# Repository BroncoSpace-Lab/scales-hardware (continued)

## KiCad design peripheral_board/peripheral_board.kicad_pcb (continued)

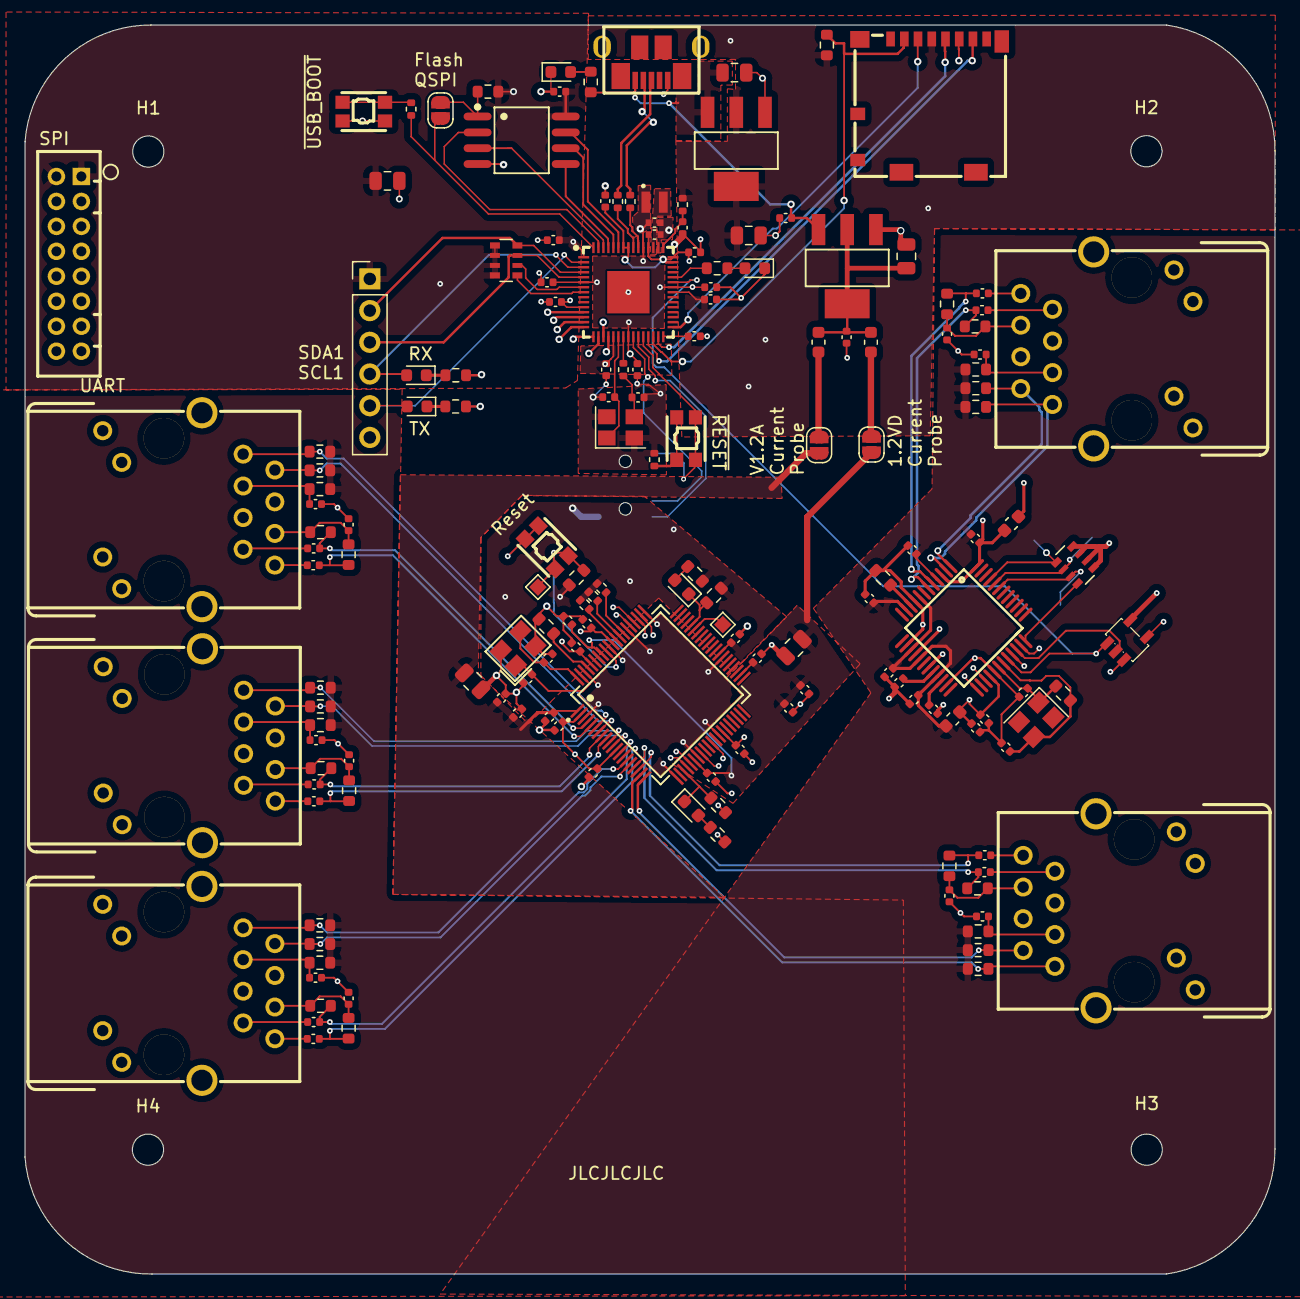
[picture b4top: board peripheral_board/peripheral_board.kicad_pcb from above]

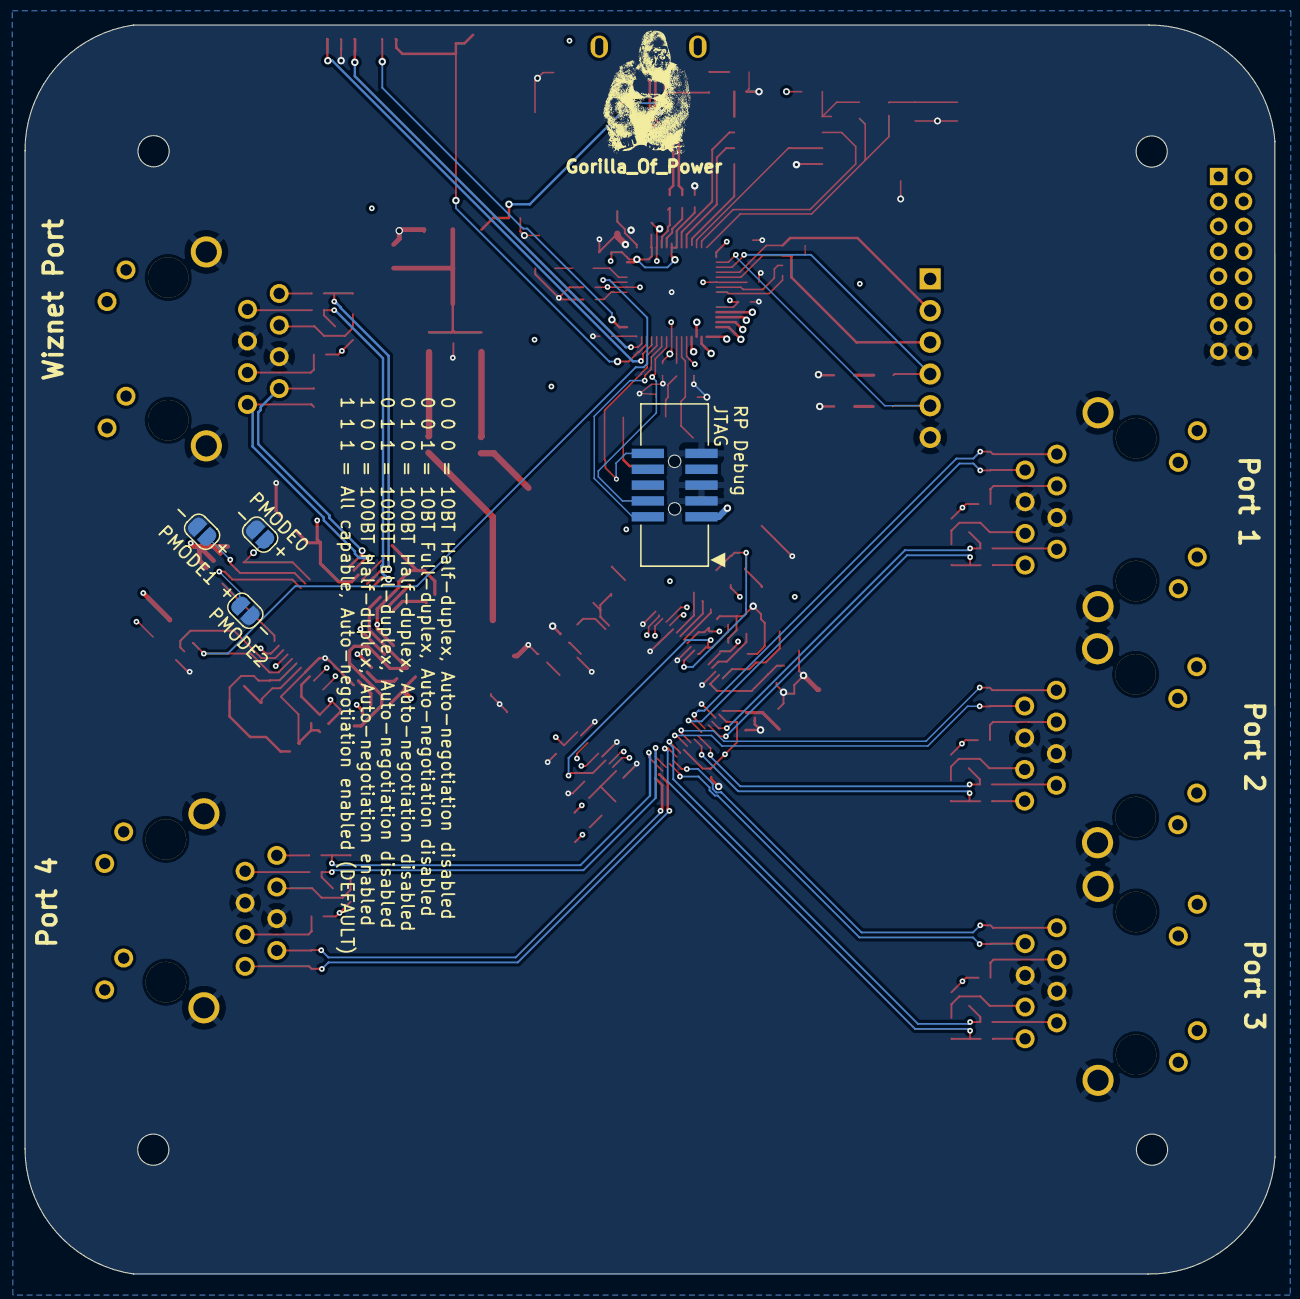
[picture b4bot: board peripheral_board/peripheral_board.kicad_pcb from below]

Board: 4 copper layers, 100.2 x 100.1 mm, 168 parts (5 on the bottom side), 128 nets.

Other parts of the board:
Gorilla_Of_Power: LOGO

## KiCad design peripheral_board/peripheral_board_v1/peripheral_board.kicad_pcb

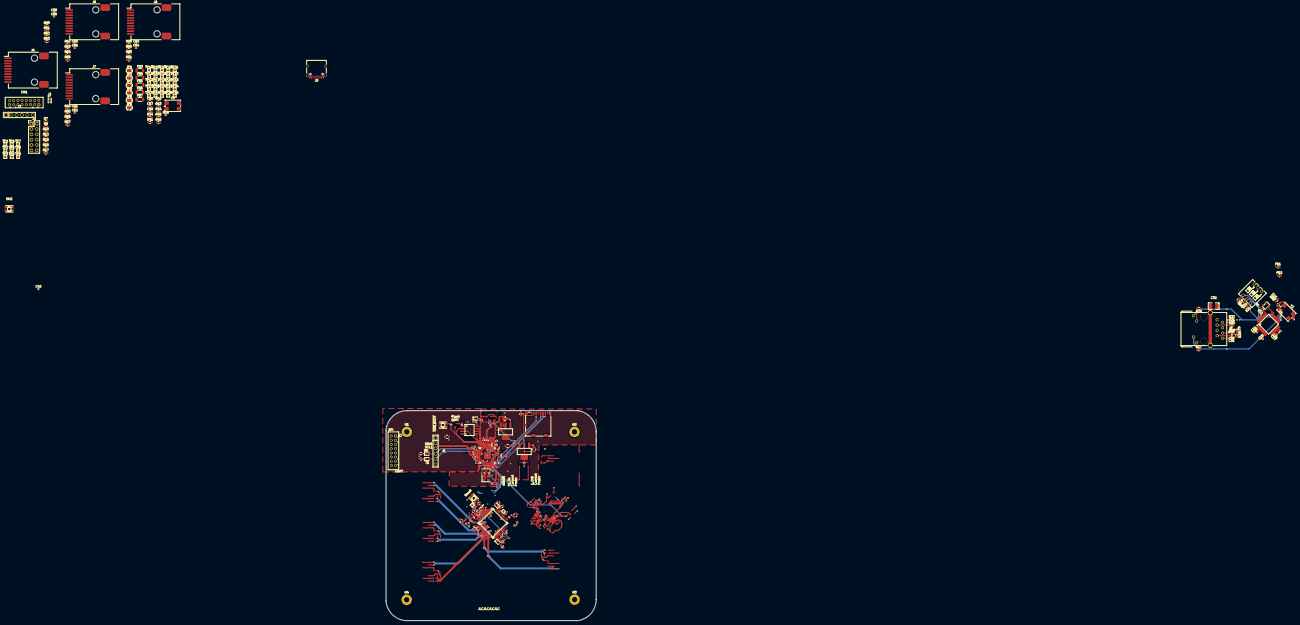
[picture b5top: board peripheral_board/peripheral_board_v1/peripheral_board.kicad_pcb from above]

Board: 4 copper layers, 100.2 x 100.1 mm, 218 parts (1 on the bottom side), 185 nets.

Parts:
C1, C2: 4.7uF; C_0402_1005Metric_small_pads
C3, C8, C9, C10, C11, C12, C13, C14, C15, C19, C34, C35, C36, C37, C38, C40, C41, C42, C45, C46, C49, C50, C51, C54, C55: 100nF; C_0402_1005Metric
C4, C5: 15pF; C_0402_1005Metric
C6, C7: 4.7uF; C_0402_1005Metric
C16, C18: 10uF; C_0805_2012Metric
C17: 22uF; C_0805_2012Metric
C20, C28: 10uF; C_0402_1005Metric
C21, C23, C24, C26, C27, C59, C60, C61, C62, C63, C64, C65, C66: 0.1uF; C_0402_1005Metric
C22, C25, C52, C53: 18pF; C_0402_1005Metric
C29, C33, C47, C48: 10nF; C_0402_1005Metric
C30, C31: 6.8nF; C_0402_1005Metric
C32: 1nF/2kV; C1210
C39, C43, C44: 100uF; C_0805_2012Metric
C56: 10uF; C_0603_1608Metric
C57, C58: 22uF; C_0603_1608Metric
CN1: Power Board Connector; CONN-TH_DF11-16DP-2DSA-08
CN2: DF11-16DP-2DSA(08); CONN-TH_DF11-16DP-2DSA-08
D1, D2, D3, D4, D5: LED; LED_0603_1608Metric
FB1, FB2: HH-1M1608-121JT; L_0603_1608Metric
FB3, FB4, FB5, FB6, FB7: FerriteBead; L_1206_3216Metric
Gorilla_Of_Power: LOGO
H1, H2, H3, H4: MountingHole; MountingHole_2.5mm_Pad
J1: Conn_01x03_Pin; PinHeader_1x03_P1.00mm_Vertical
J2, J4: Conn_01x06; HDR-TH_6P-P2.54-V-M-1
J3: Conn_02x06_Odd_Even; PinHeader_2x06_P2.54mm_Vertical
J5: USB_C_Receptacle_USB2.0_16P; USB_C_Receptacle_HRO_TYPE-C-31-M-12
J6, J7, J8, J9: RJ45_Pulse_JXD6-0001NL; RJ45_Pulse_JXD6-0001NL_Horizontal
JP1, JP2, JP3, JP4, JP5, JP6: SolderJumper_2_Open; SolderJumper-2_P1.3mm_Open_RoundedPad1.0x1.5mm
L1: 3.3uH; IND-SMD_L2.0-W1.6_AOTA-B201610S3R3-101-T
R1, R3, R4: 1k; R_0402_1005Metric
R2: 33; R_0402_1005Metric
R5, R6: 27; R_0402_1005Metric
R7, R8, R9, R10, R12, R14, R19, R20, R21, R49: 10k; R_0603_1608Metric
R11, R13, R50, R51, R52, R53, R54, R55, R56, R57, R58, R59, R60, R61, R62, R63, R64, R65: 1k; R_0603_1608Metric
R15, R34: 0; R_0603_1608Metric
R16, R17: 5.1k; R_0603_1608Metric
R18, R40: 12.4k; R_0603_1608Metric
R22, R23, R24, R33, R39: 4.7k; R_0603_1608Metric
R25: 1M; R_0603_1608Metric
R26, R28, R31, R32: 49.9; R_0603_1608Metric
R27, R29, R47, R48: 330; R_0603_1608Metric
R30: 10; R_0603_1608Metric
R35, R37: 10k; R_0402_1005Metric
R36: 4.7k; R_0402_1005Metric
R38: 350; R_0402_1005Metric
R41, R42, R43, R44, R45, R46: 750; R_0603_1608Metric
RJ1: RB1-125BAG1A; RJ45-TH_RB1-125BAG1A
SIM1: 1040310811; SIM-SMD_8P-1040310811
SW1, SW2, SW4: EVPAA602W; KEY-TH_4P-L3.5-W4.9-P2.80-LS4.3
SW3: 3_Pin_Dip_Switch_DSWB03LHGET_C25503178; SW-TH_DSWB03LHGET
TP1, TP2, TP3, TP4, TP5, TP6, TP7, TP8, TP9, TP10, TP11, TP12, TP13, TP14, TP15, TP16, TP17, TP18, TP19, TP20, TP21, TP22, TP23, TP24, TP25, TP26, TP27, TP28, TP29, TP30, TP31, TP32, TP33, TP34, TP35, TP36: TestPoint; TestPoint_Pad_1.0x1.0mm
U1: RP2350A_C42411118; QFN-60_L7.0-W7.0-P0.40-TL-EP3.4
U2: AZ1117CH-3.3TRG1; SOT-223-3_L6.5-W3.4-P2.30-LS7.0-BR
U3: W25Q128JVSIQTR; SOIC-8_L5.3-W5.3-P1.27-LS8.0-BL
U4: W5500; LQFP-48_L7.0-W7.0-P0.50-LS9.0-BL
U5: SN74AHC1G125DBVR; SOT-23-5_L3.0-W1.7-P0.95-LS2.8-BR
U6: AZ1117CH-1.2TRG1; SOT-223-3_L6.5-W3.4-P2.30-LS7.0-BR
U7: KSZ8795CLXIC; LQFP-80_L10.0-W10.0-P0.40-LS12.2-BL
Y1: ABM8-272-T3; Crystal_SMD_3225-4Pin_3.2x2.5mm
Y2: 25MHz; Crystal_SMD_7050-4Pin_7.0x5.0mm
Y3: ABMM-25.000MHZ-B2-T; Crystal_SMD_7050-4Pin_7.0x5.0mm

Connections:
1.2A: C41.2, C43.2, C45.2, C47.2, FB3.2, U7.1 (VDD12A)
1.2D: C35.2, C44.2, C46.2, C48.2, C50.2, C51.2, FB4.2, U7.26 (VDD12D), U7.42 (VDD12D), U7.73 (VDD12D)
3V3A: C23.2, C24.2, C26.2, C27.2, C28.2, FB1.2, R30.2, R31.2, R32.2, U4.4 (AVDD), U4.8 (AVDD), U4.11 (AVDD), U4.15 (AVDD), U4.17 (AVDD), U4.21 (AVDD)
+1V1: C2.1, C3.1, C6.1, C8.1, L1.1, U1.6 (DVDD), U1.23 (DVDD), U1.39 (DVDD), U1.50 (VREG_FB)
+3V3: C1.1, C9.1, C10.1, C11.1, C12.1, C13.1, C14.1, C15.1, C17.2, C18.1, C19.1, CN2.1, CN2.2, FB1.1, FB6.1, FB7.1, J2.1, J3.1, J3.2, J4.1, R2.2, R7.2, R9.2, R10.2, R12.2, R14.2, R15.2, R19.2, R20.2, R21.2, R22.2, R23.2, R24.2, R27.2, R29.1, R47.2, R48.2, R50.2, R52.2, R54.2, R56.2, R58.2, R60.2, R62.2, R64.2, SIM1.4 (VDD), U1.1 (IOVDD), U1.11 (IOVDD), U1.20 (IOVDD), U1.30 (IOVDD), U1.38 (IOVDD), U1.44 (ADC_AVDD), U1.45 (IOVDD), U1.49 (VREG_VIN), U1.53 (USB_OTP_VDD), U1.54 (QSPI_IOVDD), U2.2 (Vout), U2.4 (Vout), U3.1 (~CS), U3.8 (VCC), U4.28 (VDD), U5.5 (VCC)
/Raspberry_pi/ QSPI_SS: R1.1, R15.1, U1.60 (QSPI_SS)
/Raspberry_pi/QSPI_DATA_0: U1.57 (QSPI_SD0), U3.5 (DI)
/Raspberry_pi/QSPI_DATA_1: U1.59 (QSPI_SD1), U3.2 (DO)
/Raspberry_pi/QSPI_DATA_2: U1.58 (QSPI_SD2), U3.3 (IO2)
/Raspberry_pi/QSPI_DATA_3: U1.55 (QSPI_SD3), U3.7 (IO3)
/Raspberry_pi/QSPI_SCK: U1.56 (QSPI_SCLK), U3.6 (CLK)
/Raspberry_pi/~USB_BOOT: R1.2, SW1.1'
CGND: C32.1, RJ1.13 (GND), RJ1.14 (GND)
Chassis_GND: FB5.1, J6.SH, J7.SH, J8.SH, J9.SH
D+: J5.A6 (D+), J5.B6 (D+), R5.1
D-: J5.A7 (D-), J5.B7 (D-), R6.1
GND: C1.2, C2.2, C3.2, C4.1, C5.1, C6.2, C7.2, C8.2, C9.2, C10.2, C11.2, C12.2, C13.2, C14.2, C15.2, C16.1, C17.1, C18.2, C19.2, C22.1, C25.1, C32.2, C34.1, C35.1, C36.1, C37.1, C38.1, C39.1, C40.1, C41.1, C42.1, C43.1, C44.1, C45.1, C46.1, C47.1, C48.1, C49.1, C50.1, C51.1, C52.2, C53.2, C54.1, C55.1, C56.2, C57.2, C58.2, C59.2, C60.2, C61.2, C62.2, C63.2, C64.2, C65.2, C66.2, CN1.9, CN1.11, CN1.13, CN1.15, CN2.15, CN2.16, D1.1 (K), FB2.1, FB5.2, J1.2, J2.6, J4.6, J5.A1 (GND), J5.A12 (GND), J5.B1 (GND), J5.B12 (GND), J5.S1 (SHIELD), R11.2, R13.2, R16.1, R17.1, R38.2, R40.2, R41.2, R42.2, R43.2, R44.2, R45.2, R46.2, R51.2, R53.2, R55.2, R57.2, R59.2, R61.2, R63.2, R65.2, RJ1.4, RJ1.5, SIM1.6 (VSS), SW1.2, SW2.2, SW3.4, SW3.5, SW3.6, SW4.2, U1.47 (VREG_PGND), U1.61 (GND), U2.1 (ADJ/GND), U3.4 (GND), U4.23 (RSVD), U4.29 (GND), U5.3 (GND), U6.1 (GND), U7.3 (GNDA), U7.21 (GNDA), U7.27 (GNDD), U7.33 (GNDD), U7.47 (GNDD), U7.61 (GNDD), U7.71 (GNDD), U7.78 (GNDA), Y1.2, Y1.4, Y2.2, Y2.4, Y3.2, Y3.4
GNDA: C20.2, C21.2, C23.1, C24.1, C26.1, C27.1, C28.1, C29.1, C33.1, FB2.2, R18.1, U4.3 (AGND), U4.9 (AGND), U4.14 (AGND), U4.16 (AGND), U4.19 (AGND), U4.48 (AGND)
GPIO14: CN1.14, U1.18 (GPIO14)
GPIO15: CN1.16, U1.19 (GPIO15)
GPIO22: J3.3, U1.34 (GPIO22)
GPIO23: J3.5, U1.35 (GPIO23)
GPIO24: J3.7, U1.36 (GPIO24)
GPIO25: J3.9, U1.37 (GPIO25)
GPIO26_ADC0: J3.4, U1.40 (GPIO26_ADC0)
GPIO27_ADC1: J3.6, U1.41 (GPIO27_ADC1)
GPIO28_ADC2: J3.8, U1.42 (GPIO28_ADC2)
GPIO29_ADC3: J3.10, U1.43 (GPIO29_ADC3)
GREEN_LED: RJ1.10 (LLED-), U4.25 (LINKLED)
I2C0_SCL: J2.2, R7.1, U1.8 (GPIO5)
I2C0_SDA: J2.3, R9.1, U1.7 (GPIO4)
I2C1_SCL: J2.4, J4.3, R10.1, U1.5 (GPIO3)
I2C1_SDA: J2.5, J4.2, R12.1, U1.4 (GPIO2)
INTR_N: D4.1 (K), R33.2, U7.23 (INTR_N)
INTn: R23.1, U1.33 (GPIO21), U4.36 (INTn)
LED1_0: J6.1, J6.9, JP1.1 (A), R51.1, R53.1, U7.65 (LED10)
LED1_1: JP2.1 (A), U7.64 (LED11)
LED2_0: J7.1, J7.9, JP3.1 (A), R55.1, R57.1, U7.63 (LED20)
LED2_1: JP4.1 (A), U7.62 (LED21)
LED3_0: J8.1, J8.9, JP5.1 (A), R59.1, R61.1, U7.25 (LED3_0)
LED3_1: JP6.1 (A), U7.24 (LED3_1)
LED4_0: J9.1, J9.9, R63.1, R65.1, U7.31 (LED4_0)
unnamed: C5.2, R4.1, Y1.3
unnamed: C30.2, RJ1.7
unnamed: C31.2, RJ1.8
unnamed: C39.2, C40.2, C42.2, FB3.1, FB4.1, U6.2 (VOUT), U6.4 (VOUT)
unnamed: C52.1, R34.2, Y3.1
unnamed: CN1.4, TP5.1
unnamed: CN1.6, TP6.1
unnamed: CN1.8, TP7.1
unnamed: CN1.10, TP8.1
unnamed: CN1.12, TP9.1
unnamed: D1.2 (A), R8.1
unnamed: D2.1 (K), R11.1
unnamed: D3.1 (K), R13.1
unnamed: D4.2 (A), R47.1
unnamed: D5.2 (A), R48.1
unnamed: J3.11, J3.12
unnamed: J5.A5 (CC1), R16.2
unnamed: J5.B5 (CC2), R17.2
unnamed: J6.2, R52.1
unnamed: J6.10, R50.1
unnamed: J7.2, R56.1
unnamed: J7.10, R54.1
unnamed: J8.2, R60.1
unnamed: J8.10, R58.1
unnamed: J9.2, R64.1
unnamed: J9.10, R62.1
unnamed: JP1.2 (B), R41.1
unnamed: JP2.2 (B), R42.1
unnamed: JP3.2 (B), R43.1
unnamed: JP4.2 (B), R44.1
unnamed: JP5.2 (B), R45.1
unnamed: JP6.2 (B), R46.1
unnamed: R3.2, SW2.1'
unnamed: R29.2, RJ1.9 (LLED+)
unnamed: R27.1, RJ1.11 (RLED+)
unnamed: SW1.1, TP2.1
unnamed: SW1.2', TP3.1
unnamed: SW2.1, TP1.1
unnamed: SW2.2', TP4.1
unnamed: SW4.1', TP35.1
unnamed: SW4.2', TP36.1
unnamed: R3.1, U1.26 (RUN)
unnamed: R6.2, U1.51 (USB_DM)
unnamed: R5.2, U1.52 (USB_DP)
unnamed: C7.1, R2.1, U1.46 (VREG_AVDD)
unnamed: L1.2, U1.48 (VREG_LX)
unnamed: C4.2, U1.21 (XIN), Y1.1
unnamed: R4.2, U1.22 (XOUT)
unnamed: C21.1, U4.22 (1V2O)
unnamed: R18.2, U4.10 (EXRES1)
unnamed: C20.1, U4.20 (TOCAP)
unnamed: C22.2, R25.1, U4.30 (XI/CLKIN), Y2.1
unnamed: C25.2, R25.2, U4.31 (XO), Y2.3
unnamed: TP24.1, U7.54 (COL5)
unnamed: TP25.1, U7.53 (CRS5)
unnamed: R40.1, U7.77 (ISET)
unnamed: TP23.1, U7.55 (REFCLKO)
unnamed: TP32.1, U7.44 (RXC5/GRXC5)
unnamed: TP31.1, U7.45 (RXD5_0)
unnamed: TP30.1, U7.46 (RXD5_1)
unnamed: TP29.1, U7.49 (RXD5_2)
unnamed: TP28.1, U7.50 (RXD5_3)
unnamed: TP22.1, U7.57 (RXD5_4)
unnamed: TP21.1, U7.58 (RXD5_5)
unnamed: TP20.1, U7.59 (RXD5_6)
unnamed: TP19.1, U7.60 (RXD5_7)
unnamed: TP27.1, U7.51 (RXDV5/CRSDV5/RXD5_CTL)
unnamed: TP26.1, U7.52 (RXER5)
unnamed: R37.1, U7.67 (SCL_MDC)
unnamed: R36.1, U7.68 (SDA_MDIO)
unnamed: R38.1, U7.66 (SPIQ)
unnamed: R35.1, U7.69 (SPIS_N)
unnamed: TP33.1, U7.43 (TXC5/REFCLKI5/GTXC5)
unnamed: TP11.1, U7.30 (TXD5_0)
unnamed: TP12.1, U7.32 (TXD5_1)
unnamed: TP13.1, U7.35 (TXD5_2)
unnamed: TP14.1, U7.36 (TXD5_3)
unnamed: TP16.1, U7.38 (TXD5_4)
unnamed: TP17.1, U7.39 (TXD5_5)
unnamed: TP18.1, U7.40 (TXD5_6)
unnamed: TP34.1, U7.41 (TXD5_7)
unnamed: TP10.1, U7.29 (TXEN5/TXDS5_CTL)
unnamed: TP15.1, U7.37 (TXER5)
unnamed: C53.1, U7.79 (XI), Y3.3
unnamed: R34.1, U7.80 (XO)
PME_N: D5.1 (K), R39.2, U7.56 (PME)
PMODE0: R21.1, SW3.1, U4.45 (PMODE0)
PMODE1: R20.1, SW3.2, U4.44 (PMODE1)
PMODE2: R19.1, SW3.3, U4.43 (PMODE2)
R1CT: C60.1, J6.8 (RCT)
R2CT: C62.1, J7.8 (RCT)
R3CT: C64.1, J8.8 (RCT)
R4CT: C66.1, J9.8 (RCT)
RCT: C29.2, R26.1, R28.1, RJ1.6
RST_N: C56.1, R49.2, SW4.1, U7.72 (RST_N)
RSTn: R22.1, U1.32 (GPIO20), U4.37 (RSTn)
RX: D2.2 (A), J4.4, U1.3 (GPIO1)
RX1+: J6.6 (RD+), U7.4 (RXP1)
RX1-: J6.7 (RD-), U7.5 (RXM1)
RX2+: J7.6 (RD+), U7.8 (RXP2)
RX2-: J7.7 (RD-), U7.9 (RXM2)
RX3+: J8.6 (RD+), U7.13 (RXP3)
RX3-: J8.7 (RD-), U7.14 (RXM3)
RX4+: J9.6 (RD+), U7.17 (RXP4)
RX4-: J9.7 (RD-), U7.18 (RXM4)
RX +: C30.1, R26.2, U4.6 (RXP)
RX -: C31.1, R28.2, U4.5 (RXN)
SPI0_CS1: R24.1, U4.32 (SCSn)
SPI0_CSO: R14.1, SIM1.2 (CD/DAT3), U1.28 (GPIO17)
SPI0_ETHER: U4.34 (MISO), U5.2 (A)
SPI0_MISO: SIM1.7 (DAT0), U1.27 (GPIO16), U5.4 (Y)
SPI0_MOSI: SIM1.3 (CMD), U1.31 (GPIO19), U4.35 (MOSI)
SPI0_SCK: SIM1.5 (CLK), U1.29 (GPIO18), U4.33 (SCLK), U5.1 (~OE)
SPI1_CS1: CN2.12, U1.17 (GPIO13)
SPI1_RX: CN2.8, U1.16 (GPIO12)
SPI1_SCK: CN2.10, U1.14 (GPIO10)
SPI1_TX: CN2.14, U1.15 (GPIO11)
SWCLK: J1.1, U1.24 (SWCLK)
T1CT: C59.1, J6.3 (TCT)
T2CT: C61.1, J7.3 (TCT)
T3CT: C63.1, J8.3 (TCT)
T4CT: C65.1, J9.3 (TCT)
TCT: C33.2, R30.1, RJ1.3
TX: D3.2 (A), J4.5, U1.2 (GPIO0)
TX1+: J6.4 (TD+), U7.6 (TXP1)
TX1-: J6.5 (TD-), U7.7 (TXM1)
TX2+: J7.4 (TD+), U7.10 (TXP2)
TX2-: J7.5 (TD-), U7.11 (TXM2)
TX3+: J8.4 (TD+), U7.15 (TXP3)
TX3-: J8.5 (TD-), U7.16 (TXM3)
TX4+: J9.4 (TD+), U7.19 (TXP4)
TX4-: J9.5 (TD-), U7.20 (TXM4)
TX +: R32.1, RJ1.1, U4.2 (TXP)
TX -: R31.1, RJ1.2, U4.1 (TXN)
UART1_CTS: CN2.7, U1.9 (GPIO6)
UART1_RTS: CN2.9, U1.10 (GPIO7)
UART1_RX: CN2.5, U1.13 (GPIO9)
UART1_TX: CN2.3, U1.12 (GPIO8)
VBUS: C16.2, C34.2, J5.A4 (VBUS), J5.A9 (VBUS), J5.B4 (VBUS), J5.B9 (VBUS), R8.2, U2.3 (Vin), U6.3 (INPUT)
VCC: CN1.1, CN1.3, CN1.5, CN1.7
VDDAT: C37.2, C38.2, C49.2, C57.1, FB6.2, U7.2 (VDDAT33), U7.12 (VDDAT33), U7.76 (VDDAT33)
VDDIO: C36.2, C54.2, C55.2, C58.1, FB7.2, R33.1, R35.2, R36.2, R37.2, R39.1, R49.1, U7.34 (VDDIO), U7.48 (VDDIO), U7.70 (VDDIO)
YELLOW_LED: RJ1.12 (RLED-), U4.27 (ACTLED)

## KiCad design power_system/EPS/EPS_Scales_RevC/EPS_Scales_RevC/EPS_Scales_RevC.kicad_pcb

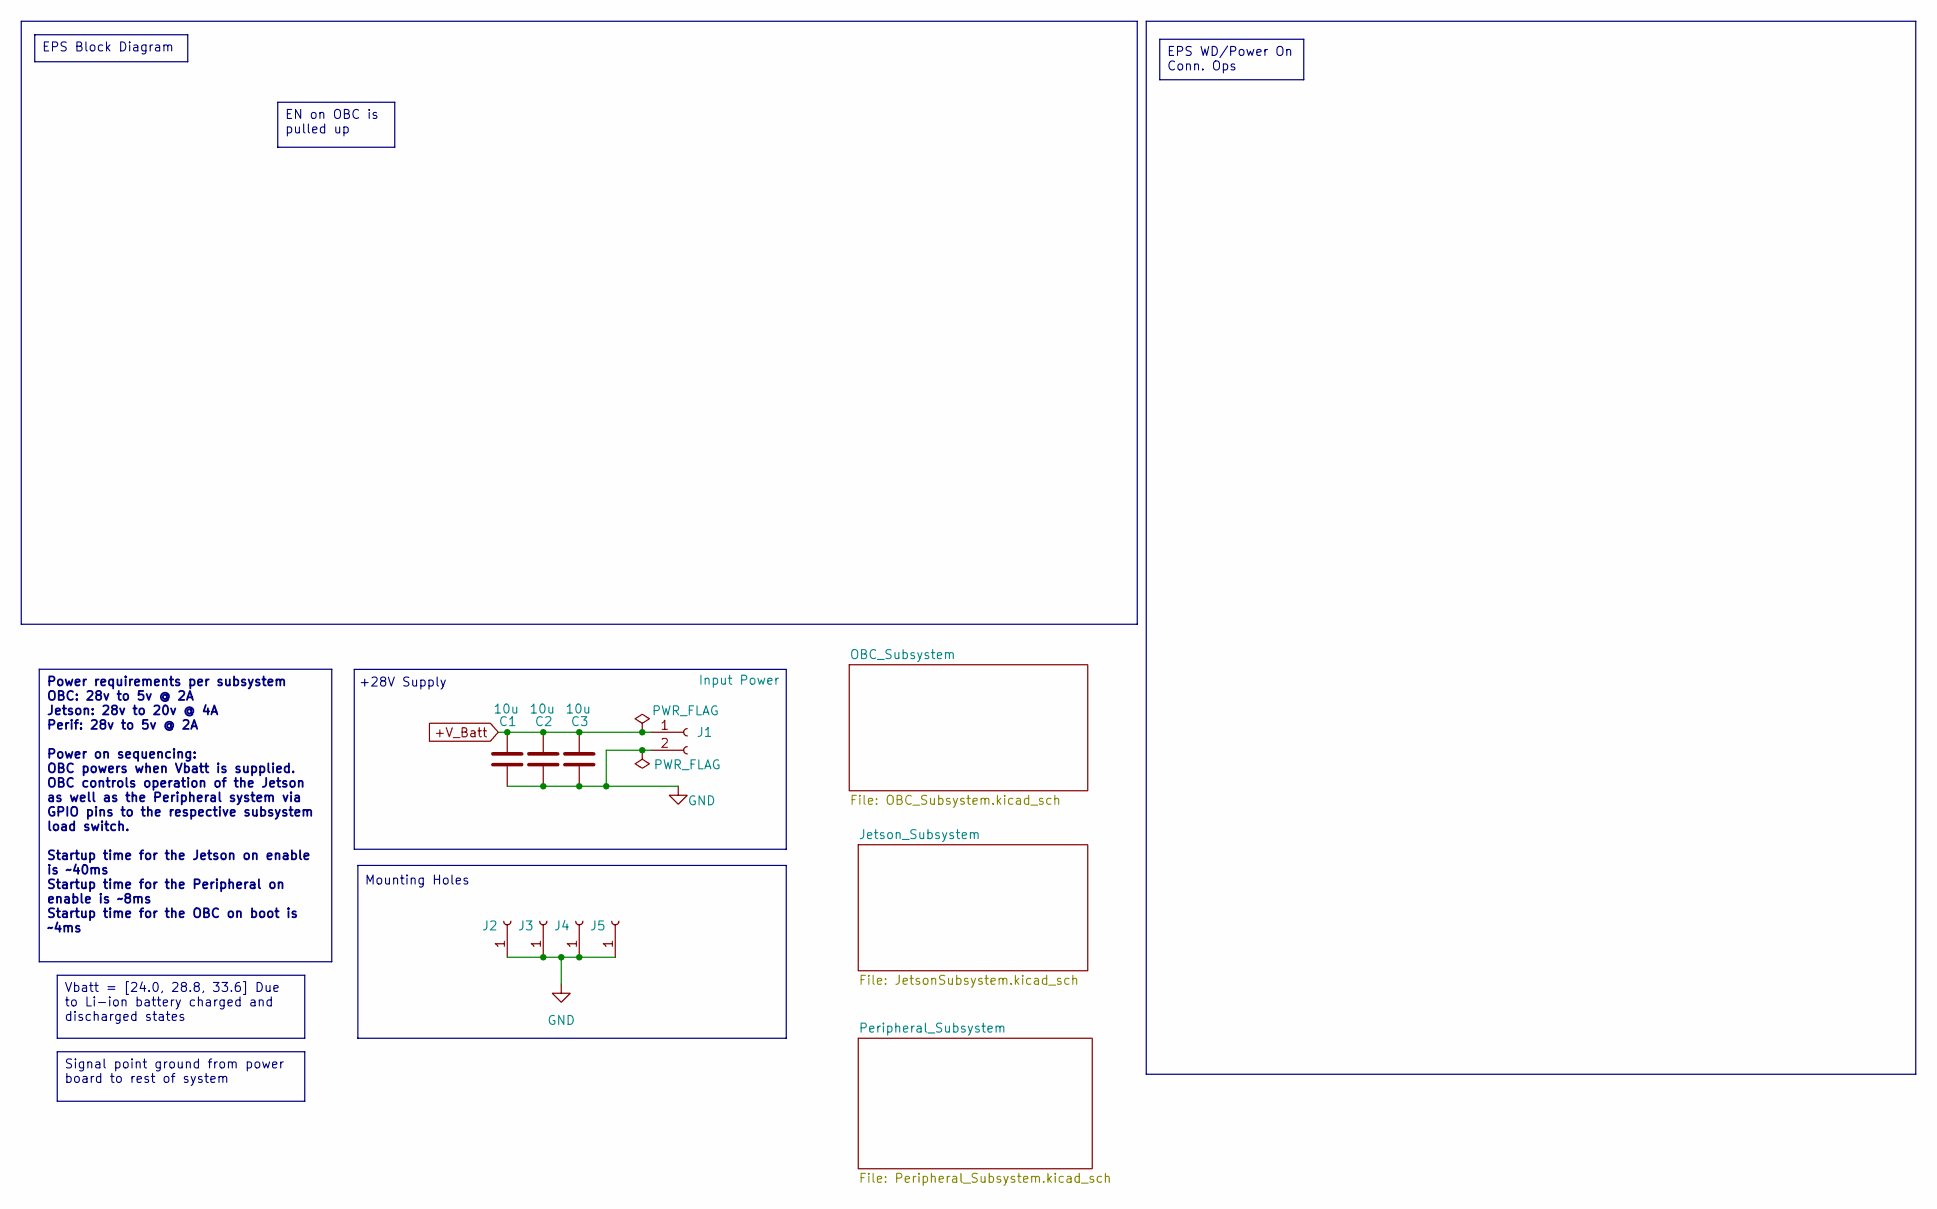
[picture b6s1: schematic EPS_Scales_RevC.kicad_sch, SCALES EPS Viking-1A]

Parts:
C1, C2, C3: 10u; C_1210_3225Metric
J1: Input Power; AMASS_XT60PW-F_1x02_P7.20mm_Horizontal
J2, J3, J4, J5: Conn_01x01_Socket; MountingHole_2.5mm_Pad_Via

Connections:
+V_Batt: C1.1, C2.1, C3.1, J1.1; also elsewhere on the board
GND: C1.2, C2.2, C3.2, J1.2, J2.1, J3.1, J4.1, J5.1; also elsewhere on the board

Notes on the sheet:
Mounting Holes
+28V Supply
Signal point ground from power board to rest of system
EPS Block Diagram
Power requirements per subsystem OBC: 28v to 5v @ 2A Jetson: 28v to 20v @ 4A Perif: 28v to 5v @ 2A Power on sequencing: OBC powers when Vbatt is supplied. OBC controls operation of the Jetson as well as the Peripheral system via GPIO pins to the respective subsystem load switch. Startup time for th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
Vbatt = [24.0, 28.8, 33.6] Due to Li-ion battery charged and discharged states
EPS WD/Power On Conn. Ops
EN on OBC is pulled up

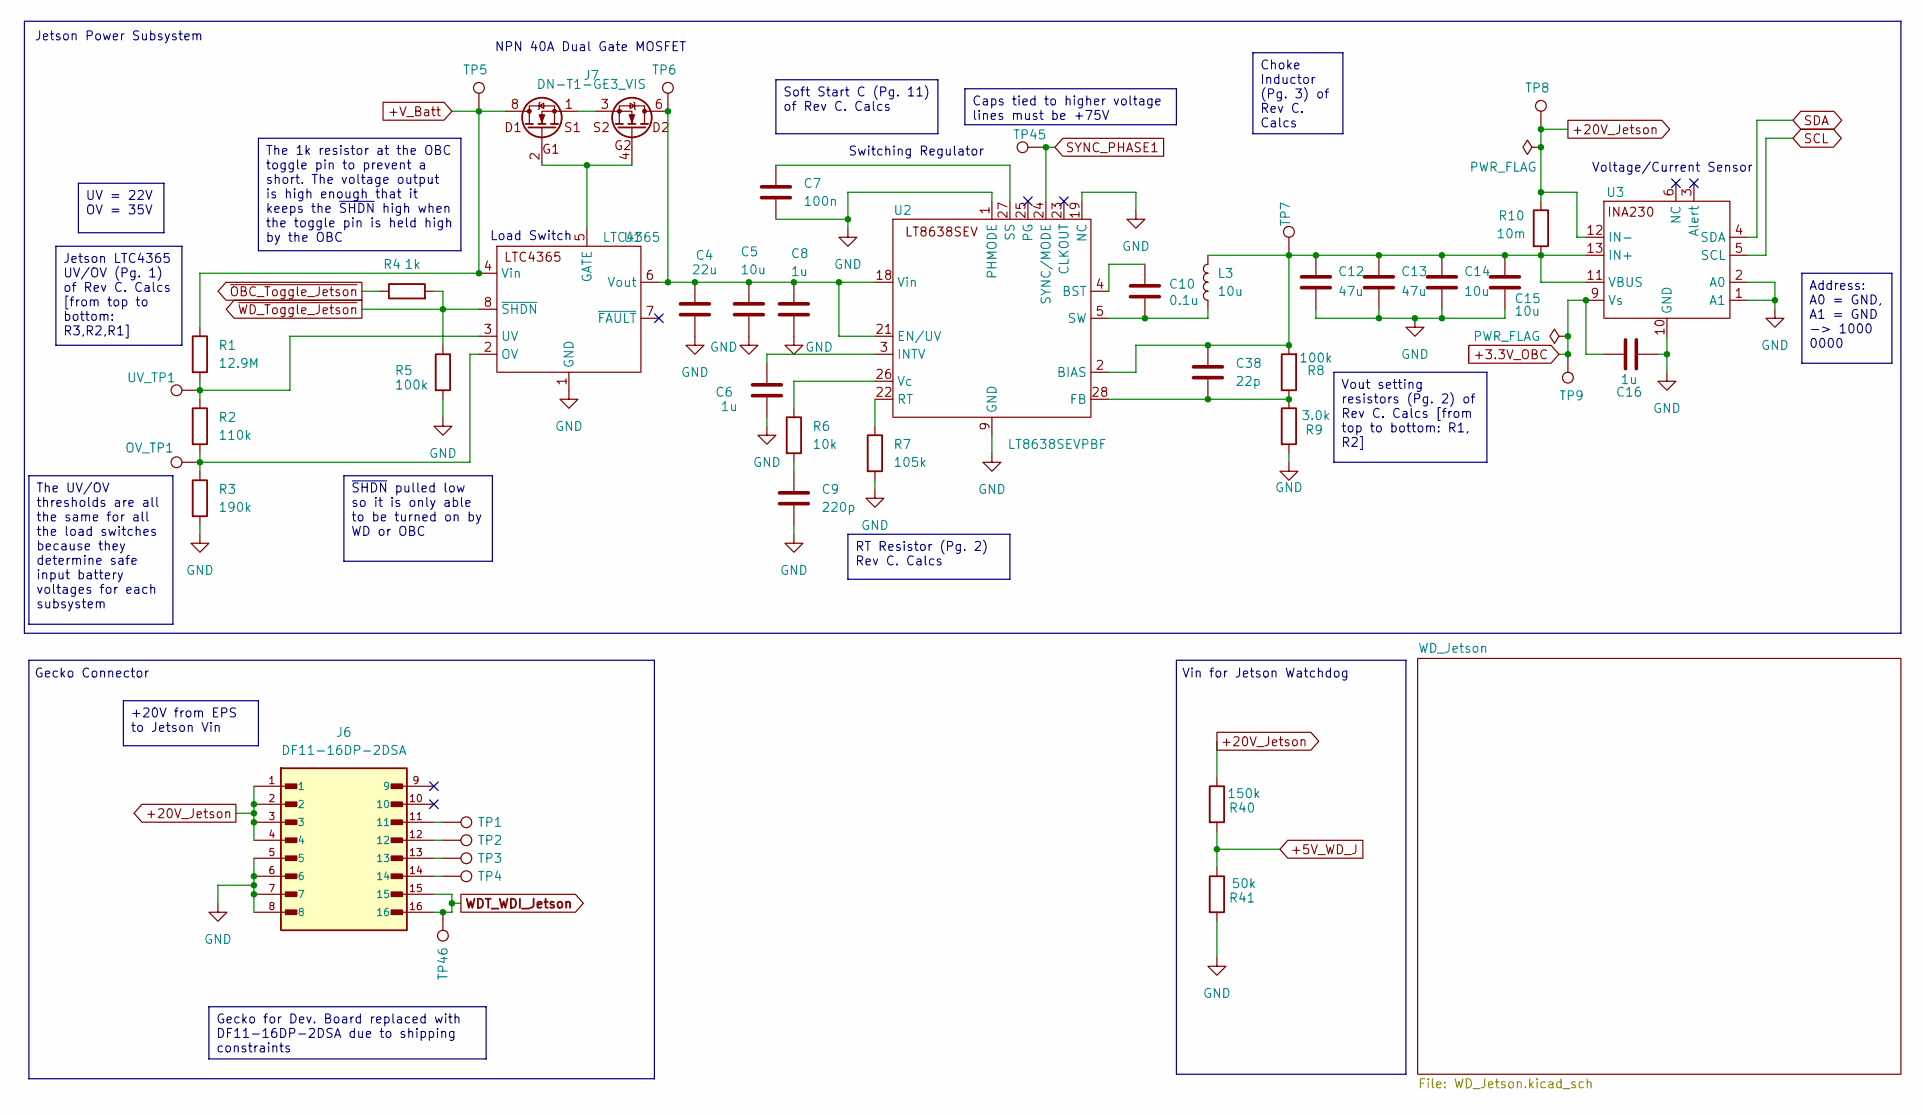
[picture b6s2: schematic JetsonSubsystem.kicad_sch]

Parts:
C4: 22u; C_1210_3225Metric; LCSC C309062
C5, C14, C15: 10u; C_1210_3225Metric
C6: 1u; C_0603_1608Metric; LCSC C304010
C7: 100n; C_0603_1608Metric
C8, C16: 1u; C_1210_3225Metric; LCSC C304010
C9: 220p; C_0603_1608Metric
C10: 0.1u; C_1210_3225Metric; LCSC C436244
C12, C13: 47u; C_1210_3225Metric
C38: 22p; C1206
J6: DF11-16DP-2DSA; DF1116DP2DSA08
J7: DN-T1-GE3_VIS; SISB46DN-T1-GE3
L3: 10u; IND-SMD_L13.8-W12.6_MHCC12050
OV_TP1: TestPoint; TestPoint_Pad_1.0x1.0mm
R1: 12.9M; R_0603_1608Metric
R2: 110k; R_0603_1608Metric; LCSC C25805
R3: 190k; R_0603_1608Metric; LCSC C25811
R4: 1k; R_0603_1608Metric; LCSC C13163
R5, R8: 100k; R_0603_1608Metric; LCSC C14675
R6: 10k; R_0603_1608Metric; LCSC C13564
R7: 105k; R_0603_1608Metric; LCSC C16840
R9: 3.0k; R_0603_1608Metric
R10: 10m; R_2512_6332Metric
R40: 150k; R_0603_1608Metric
R41: 50k; R_0603_1608Metric
TP1, TP2, TP3, TP4, TP5, TP6, TP7, TP8, TP9, TP45, TP46: TestPoint; TestPoint_Pad_1.0x1.0mm
U1: LTC4365; LCSC C580882
U2: LT8638SEVPBF; LCSC C3188906
U3: INA230; INA230AIRGTT; LCSC C92112
UV_TP1: TestPoint; TestPoint_Pad_1.0x1.0mm

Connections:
+5V_WD_J: R40.2, R41.1; also elsewhere on the board
+20V_Jetson: J6.1, J6.2, J6.3, J6.4, R10.1, R40.1, TP8.1, U3.12 (IN-)
+V_Batt: J7.7, J7.8, R1.1, TP5.1, U1.4 (Vin); also elsewhere on the board
GND: C4.2, C5.2, C6.2, C7.2, C8.2, C9.2, C12.2, C13.2, C14.2, C15.2, C16.1, J6.5, J6.6, J6.7, J6.8, R3.2, R5.2, R7.2, R9.2, R41.2, U1.1 (GND), U2.1 (PHMODE), U2.9 (GND), U2.19 (NC), U3.1 (A1), U3.2 (A0), U3.10 (GND); also elsewhere on the board
unnamed: C9.1, R6.2
unnamed: J6.11, TP1.1
unnamed: J6.12, TP2.1
unnamed: J6.13, TP3.1
unnamed: J6.14, TP4.1
unnamed: J7.1, J7.3
unnamed: J7.2, J7.4, U1.5 (GATE)
unnamed: OV_TP1.1, R2.2, R3.1, U1.2 (OV)
unnamed: R1.2, R2.1, U1.3 (UV), UV_TP1.1
unnamed: C4.1, C5.1, C8.1, J7.5, J7.6, TP6.1, U1.6 (Vout), U2.18 (Vin), U2.21 (EN/UV)
unnamed: C12.1, C13.1, C14.1, C15.1, C38.1, L3.2, R8.2, R10.2, TP7.1, U2.2 (BIAS), U3.11 (VBUS), U3.13 (IN+)
unnamed: C10.1, U2.4 (BST)
unnamed: C38.2, R8.1, R9.1, U2.28 (FB)
unnamed: C6.1, U2.3 (INTV)
unnamed: R7.1, U2.22 (RT)
unnamed: C7.1, U2.27 (SS)
unnamed: C10.2, L3.1, U2.5 (SW)
unnamed: R6.1, U2.26 (Vc)
SYNC_PHASE1: TP45.1, U2.24 (SYNC/MODE); also elsewhere on the board
WDT_WDI_Jetson: J6.15, J6.16, TP46.1; also elsewhere on the board
~OBC_Toggle_Jetson: R4.1; also elsewhere on the board
~WD_Toggle_Jetson: R4.2, R5.1, U1.8 (~SHDN); also elsewhere on the board

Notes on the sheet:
Switching Regulator
Jetson Power Subsystem
Gecko Connector
Vin for Jetson Watchdog
NPN 40A Dual Gate MOSFET
Load Switch
Voltage/Current Sensor
Gecko for Dev. Board replaced with DF11-16DP-2DSA due to shipping constraints
~{SHDN} pulled low so it is only able to be turned on by WD or OBC
RT Resistor (Pg. 2) Rev C. Calcs
Jetson LTC4365 UV/OV (Pg. 1) of Rev C. Calcs [from top to bottom: R3,R2,R1]
Caps tied to higher voltage lines must be +75V
Choke Inductor (Pg. 3) of Rev C. Calcs
The UV/OV thresholds are all the same for all the load switches because they determine safe input battery voltages for each subsystem
Vout setting resistors (Pg. 2) of Rev C. Calcs [from top to bottom: R1, R2]
UV = 22V OV = 35V
Soft Start C (Pg. 11) of Rev C. Calcs
+20V from EPS to Jetson Vin
Address: A0 = GND, A1 = GND -> 1000 0000
The 1k resistor at the OBC toggle pin to prevent a short. The voltage output is high enough that it keeps the ~{SHDN} high when the toggle pin is held high by the OBC

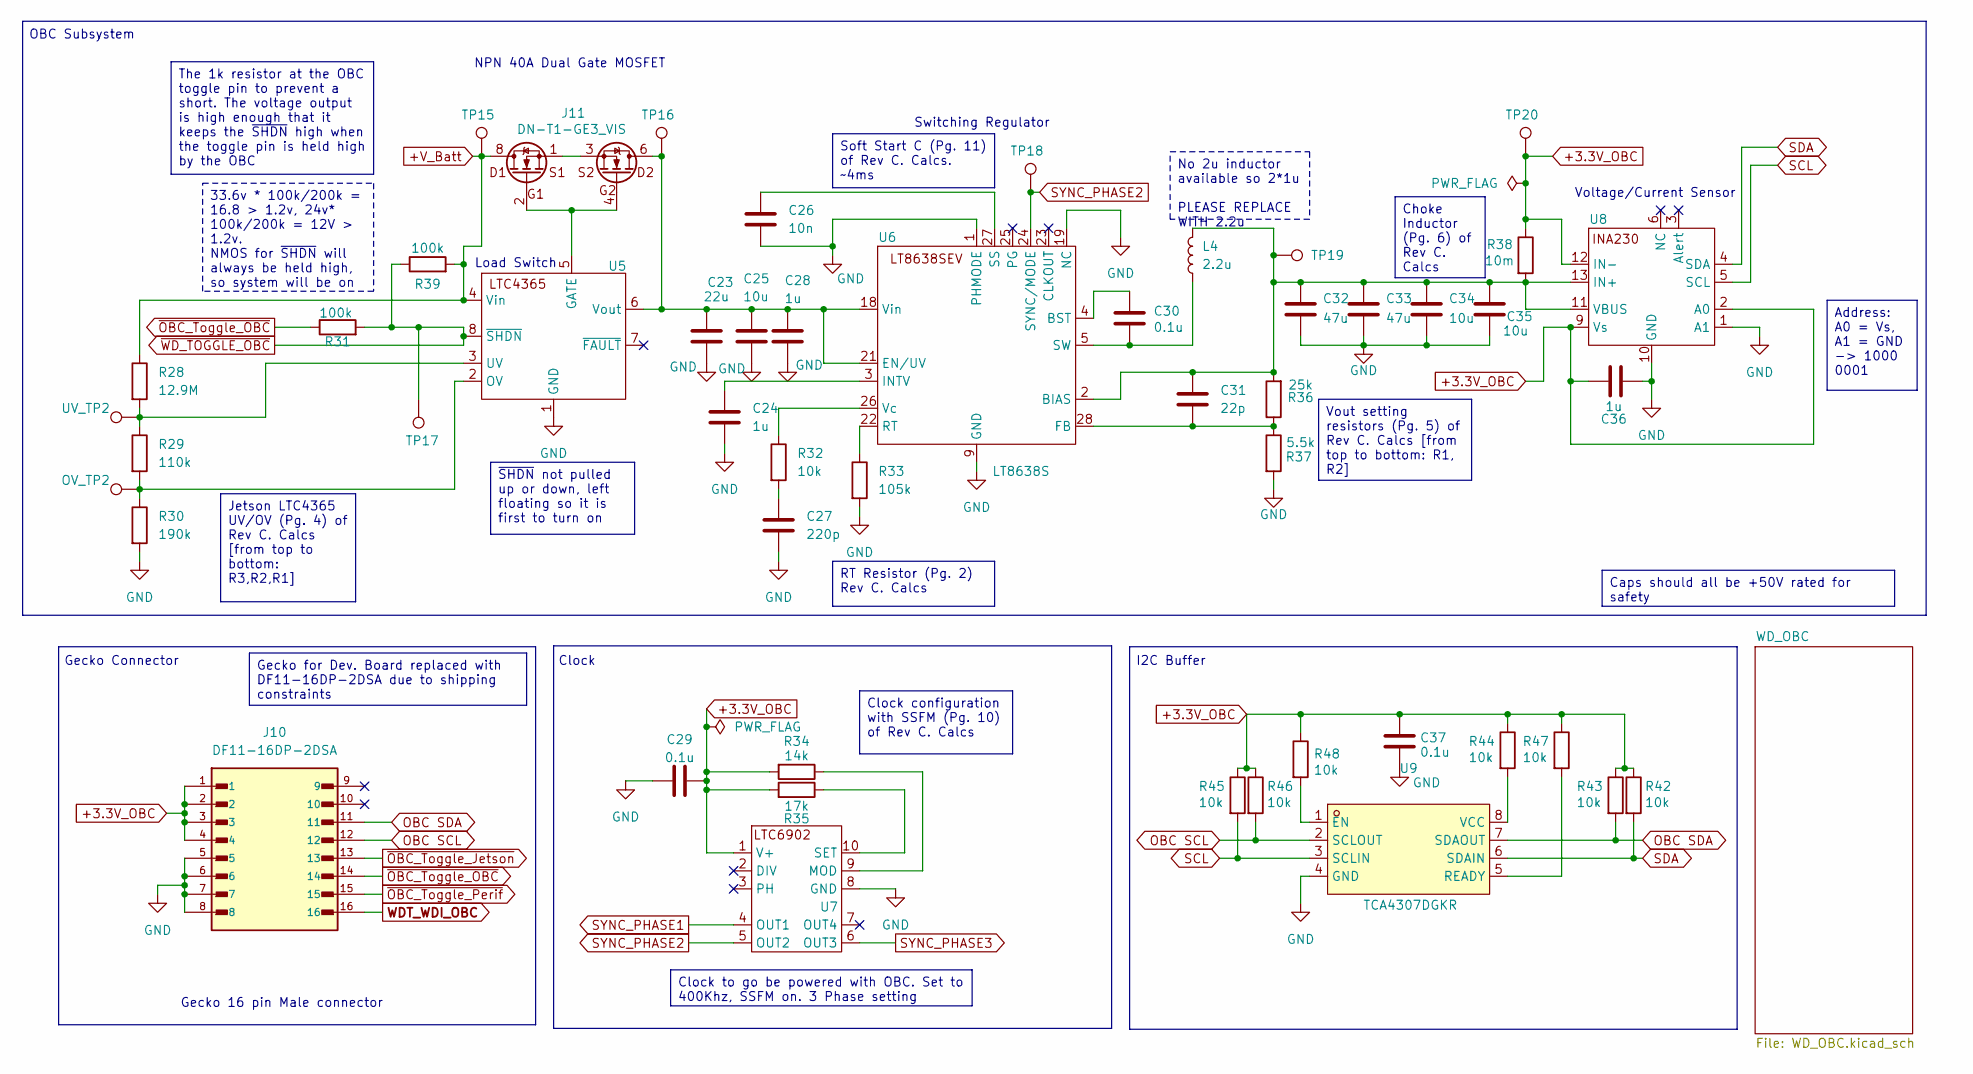
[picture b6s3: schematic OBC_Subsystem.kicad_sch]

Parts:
C23: 22u; C_1210_3225Metric; LCSC C309062
C24: 1u; C_0603_1608Metric; LCSC C304010
C25, C34, C35: 10u; C_1210_3225Metric
C26: 10n; C_0603_1608Metric
C27: 220p; C_0603_1608Metric
C28, C36: 1u; C_1210_3225Metric; LCSC C304010
C29, C30: 0.1u; C_1210_3225Metric; LCSC C436244
C31: 22p; C1206
C32, C33: 47u; C_1210_3225Metric
C37: 0.1u; C_1210_3225Metric
J10: DF11-16DP-2DSA; DF1116DP2DSA08
J11: DN-T1-GE3_VIS; SISB46DN-T1-GE3
L4: 2.2u; XEL6030; LCSC C5157561
OV_TP2: TestPoint; TestPoint_Pad_1.0x1.0mm
R28: 12.9M; R_0603_1608Metric
R29: 110k; R_0603_1608Metric; LCSC C25805
R30: 190k; R_0603_1608Metric; LCSC C25811
R31, R39: 100k; R_0603_1608Metric; LCSC C13163
R32: 10k; R_0603_1608Metric; LCSC C13564
R33: 105k; R_0603_1608Metric; LCSC C16840
R34: 14k; R_0603_1608Metric
R35: 17k; R_0603_1608Metric
R36: 25k; R_0603_1608Metric
R37: 5.5k; R_0603_1608Metric
R38: 10m; R_2512_6332Metric
R42, R43, R44, R45, R46, R47, R48: 10k; R_0603_1608Metric
TP15, TP16, TP17, TP18, TP19, TP20: TestPoint; TestPoint_Pad_1.0x1.0mm
U5: LTC4365; LCSC C580882
U6: LT8638S; LT8638SEVPBF
U7: LTC6902; LCSC C581012
U8: INA230; INA230AIRGTT
U9: TCA4307DGKR; VSSOP-8_L3.0-W3.0-P0.65-LS4.9-BL; LCSC Part C880333
UV_TP2: TestPoint; TestPoint_Pad_1.0x1.0mm

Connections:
+V_Batt: J11.7, J11.8, R28.1, R39.2, TP15.1, U5.4 (Vin); also elsewhere on the board
GND: C23.2, C24.2, C25.2, C26.2, C27.2, C28.2, C29.1, C32.2, C33.2, C34.2, C35.2, C36.1, C37.2, J10.5, J10.6, J10.7, J10.8, R30.2, R33.2, R37.2, U5.1 (GND), U6.1 (PHMODE), U6.9 (GND), U6.19 (NC), U7.8 (GND), U8.1 (A1), U8.10 (GND), U9.4 (GND); also elsewhere on the board
unnamed: C27.1, R32.2
unnamed: J11.1, J11.3
unnamed: J11.2, J11.4, U5.5 (GATE)
unnamed: OV_TP2.1, R29.2, R30.1, U5.2 (OV)
unnamed: R28.2, R29.1, U5.3 (UV), UV_TP2.1
unnamed: C23.1, C25.1, C28.1, J11.5, J11.6, TP16.1, U5.6 (Vout), U6.18 (Vin), U6.21 (EN/UV)
unnamed: C31.1, C32.1, C33.1, C34.1, C35.1, L4.2, R36.2, R38.2, TP19.1, U6.2 (BIAS), U8.11 (VBUS), U8.13 (IN+)
unnamed: C30.1, U6.4 (BST)
unnamed: C31.2, R36.1, R37.1, U6.28 (FB)
unnamed: C24.1, U6.3 (INTV)
unnamed: R33.1, U6.22 (RT)
unnamed: C26.1, U6.27 (SS)
unnamed: C30.2, L4.1, U6.5 (SW)
unnamed: R32.1, U6.26 (Vc)
unnamed: R34.1, U7.9 (MOD)
unnamed: R35.1, U7.10 (SET)
unnamed: R48.2, U9.1 (EN)
unnamed: R47.2, U9.5 (READY)
unnamed: R44.2, U9.8 (VCC)
OBC SCL: J10.12, R46.2, U9.2 (SCLOUT)
OBC SDA: J10.11, R43.2, U9.7 (SDAOUT)
SYNC_PHASE1: U7.4 (OUT1); also elsewhere on the board
SYNC_PHASE2: TP18.1, U6.24 (SYNC/MODE), U7.5 (OUT2)
SYNC_PHASE3: U7.6 (OUT3); also elsewhere on the board
WDT_WDI_OBC: J10.16; also elsewhere on the board
~OBC_Toggle_Jetson: J10.13; also elsewhere on the board
~OBC_Toggle_OBC: J10.14, R31.1
~OBC_Toggle_Perif: J10.15; also elsewhere on the board
~WD_TOGGLE_OBC: R31.2, R39.1, TP17.1, U5.8 (~SHDN); also elsewhere on the board

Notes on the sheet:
Clock
Load Switch
OBC Subsystem
NPN 40A Dual Gate MOSFET
I2C Buffer
Gecko Connector
Gecko 16 pin Male connector
Switching Regulator
Voltage/Current Sensor
No 2u inductor available so 2*1u PLEASE REPLACE WITH 2.2u
Choke Inductor (Pg. 6) of Rev C. Calcs
RT Resistor (Pg. 2) Rev C. Calcs
Jetson LTC4365 UV/OV (Pg. 4) of Rev C. Calcs [from top to bottom: R3,R2,R1]
Caps should all be +50V rated for safety
33.6v * 100k/200k = 16.8 > 1.2v, 24v* 100k/200k = 12V > 1.2v. NMOS for ~{SHDN} will always be held high, so system will be on
Soft Start C (Pg. 11) of Rev C. Calcs. ~4ms
Address: A0 = Vs, A1 = GND -> 1000 0001
Vout setting resistors (Pg. 5) of Rev C. Calcs [from top to bottom: R1, R2]
Gecko for Dev. Board replaced with DF11-16DP-2DSA due to shipping constraints
The 1k resistor at the OBC toggle pin to prevent a short. The voltage output is high enough that it keeps the ~{SHDN} high when the toggle pin is held high by the OBC
~{SHDN} not pulled up or down, left floating so it is first to turn on
Clock configuration with SSFM (Pg. 10) of Rev C. Calcs
Clock to go be powered with OBC. Set to 400Khz, SSFM on. 3 Phase setting
